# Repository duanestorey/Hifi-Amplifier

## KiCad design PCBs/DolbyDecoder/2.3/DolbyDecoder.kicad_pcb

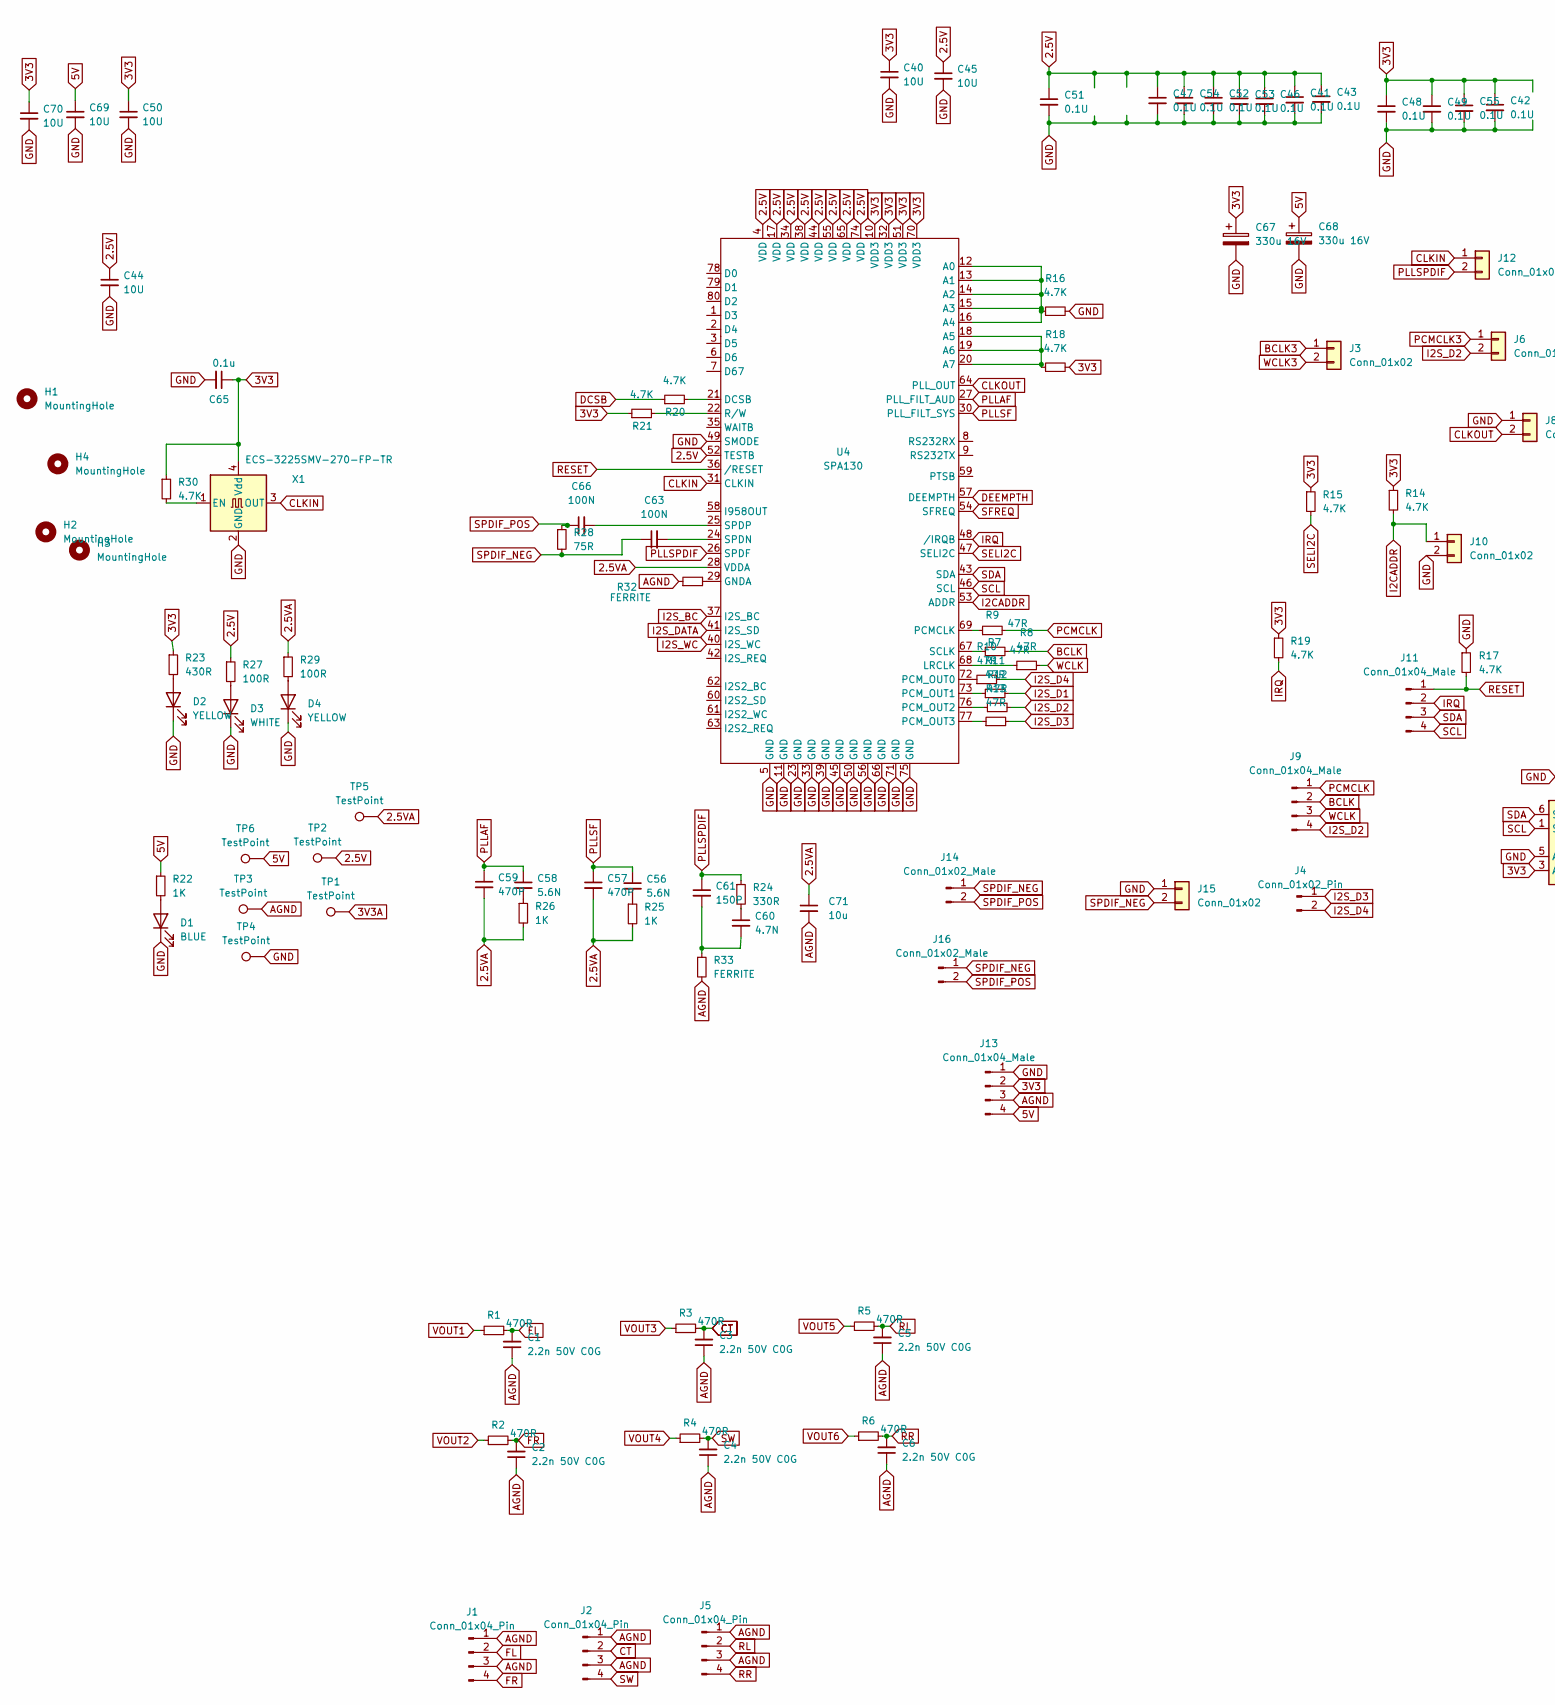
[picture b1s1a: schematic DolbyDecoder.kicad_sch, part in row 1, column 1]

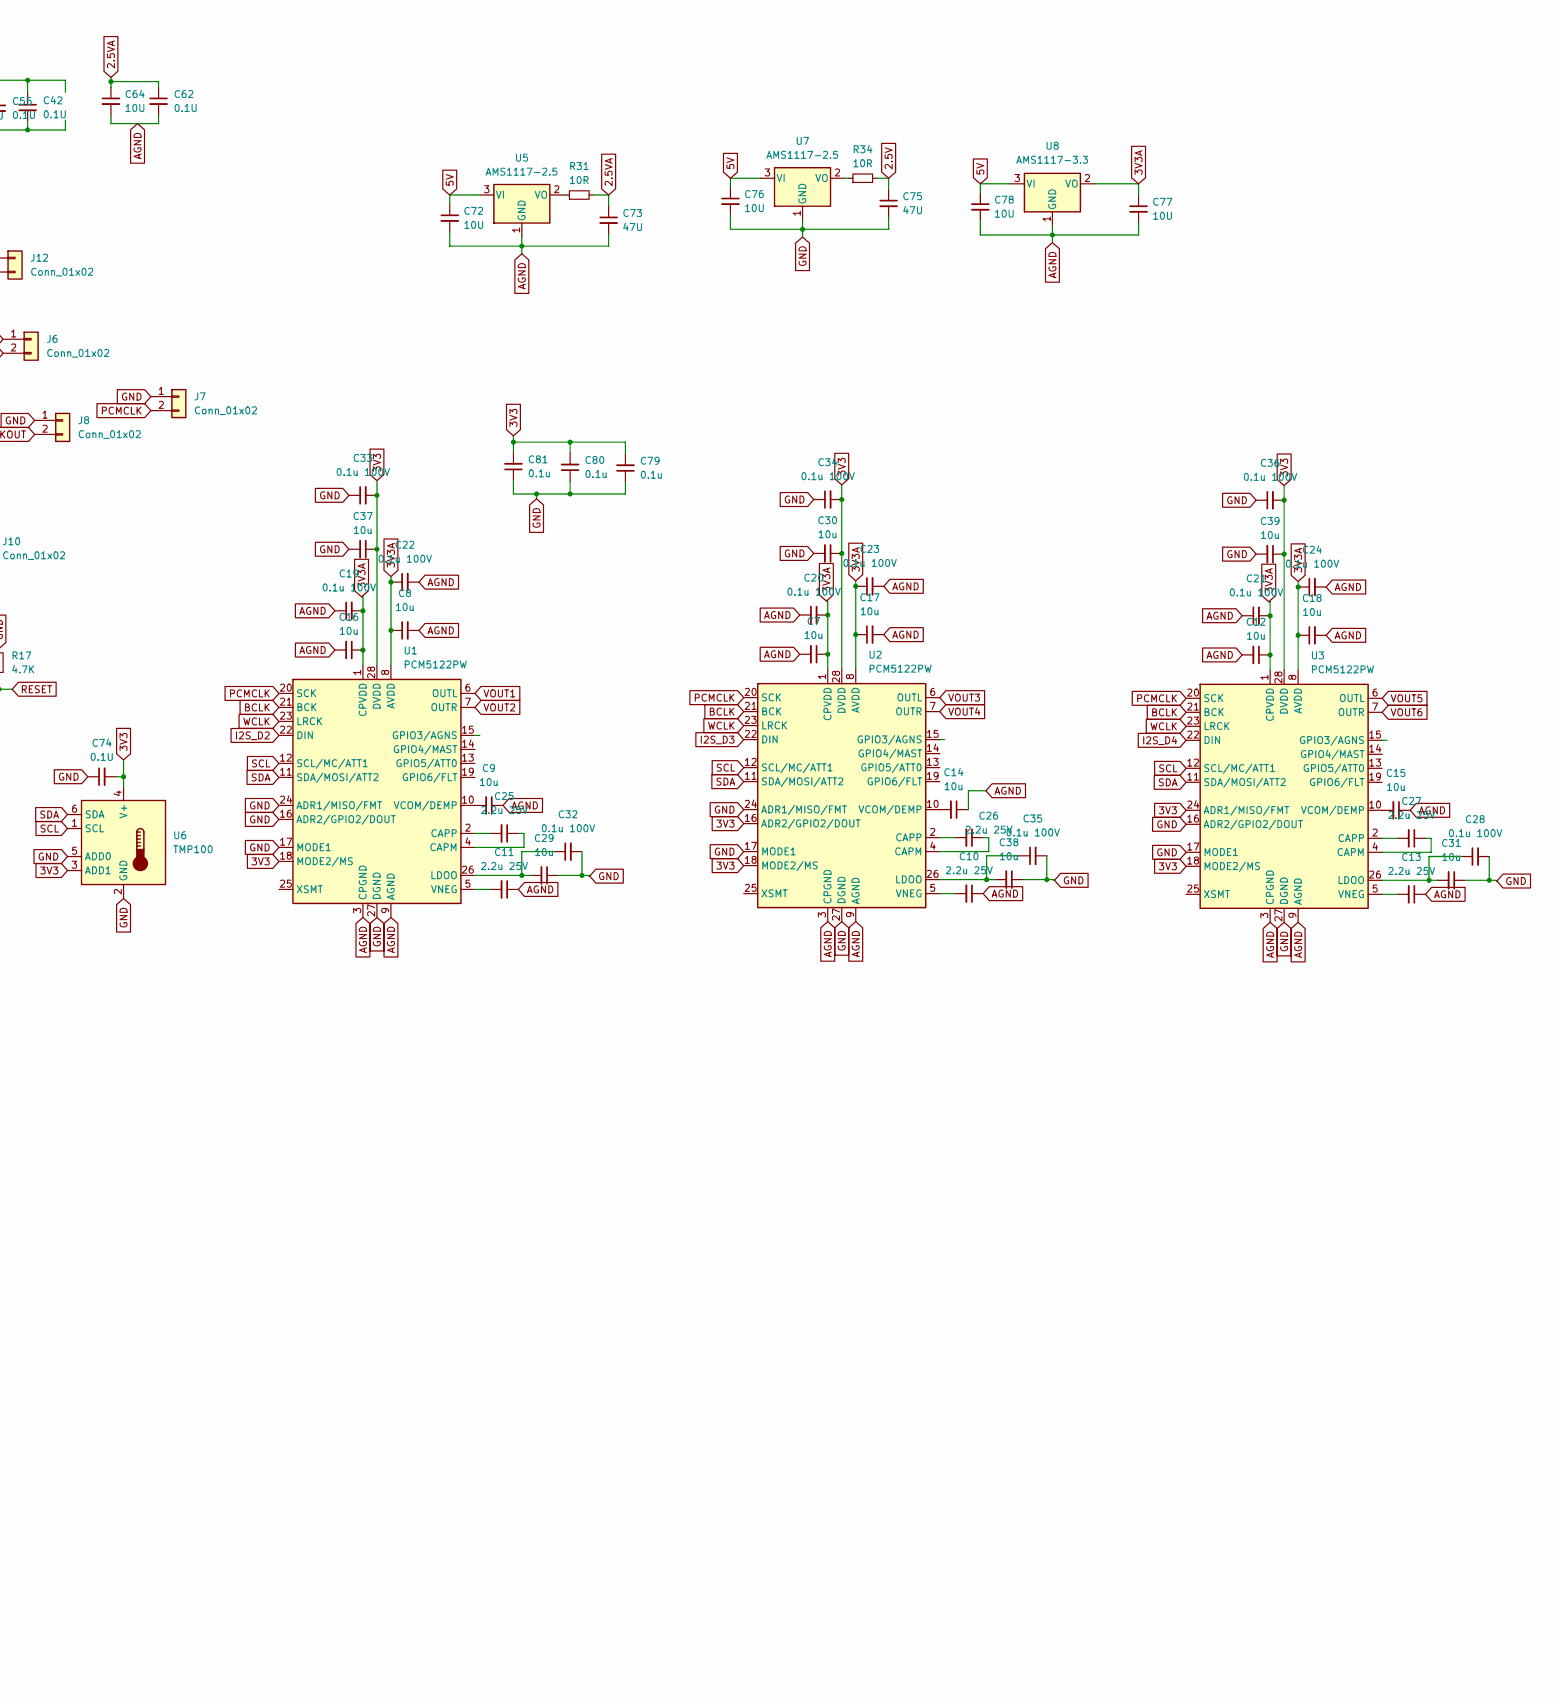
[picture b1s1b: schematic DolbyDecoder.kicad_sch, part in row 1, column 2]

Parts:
C1, C2, C3, C4, C5, C6: 2.2n 50V C0G; C_1206_3216Metric_Pad1.33x1.80mm_HandSolder
C7, C8, C9, C12, C14, C15, C16, C17, C18, C29, C30, C31, C37, C38, C39, C71: 10u; C_1206_3216Metric_Pad1.33x1.80mm_HandSolder
C10, C11, C13, C25, C26, C27: 2.2u 25V; C_1206_3216Metric_Pad1.33x1.80mm_HandSolder
C19, C20, C21, C22, C23, C24, C28, C32, C33, C34, C35, C36: 0.1u 100V; C_0805_2012Metric_Pad1.18x1.45mm_HandSolder
C40, C44, C45, C50, C64, C69, C70, C72, C76, C77, C78: 10U; C_1206_3216Metric_Pad1.33x1.80mm_HandSolder
C41, C42, C43, C46, C47, C48, C49, C51, C52, C53, C54, C55, C62, C74: 0.1U; C_0805_2012Metric_Pad1.18x1.45mm_HandSolder
C56, C58: 5.6N; C_0805_2012Metric_Pad1.18x1.45mm_HandSolder
C57, C59: 470P; C_0805_2012Metric_Pad1.18x1.45mm_HandSolder
C60: 4.7N; C_0805_2012Metric_Pad1.18x1.45mm_HandSolder
C61: 150P; C_0805_2012Metric_Pad1.18x1.45mm_HandSolder
C63, C66: 100N; C_0805_2012Metric_Pad1.18x1.45mm_HandSolder
C65, C79, C80, C81: 0.1u; C_0805_2012Metric_Pad1.18x1.45mm_HandSolder
C67, C68: 330u 16V; CP_Radial_D8.0mm_P2.50mm
C73, C75: 47U; C_1206_3216Metric_Pad1.33x1.80mm_HandSolder
D1: BLUE; LED_0805_2012Metric_Pad1.15x1.40mm_HandSolder
D2, D4: YELLOW; LED_0805_2012Metric_Pad1.15x1.40mm_HandSolder
D3: WHITE; LED_0805_2012Metric_Pad1.15x1.40mm_HandSolder
H1, H2, H3, H4: MountingHole; MountingHole_3.2mm_M3
J1, J2, J5: Conn_01x04_Pin; JST_PH_B4B-PH-K_1x04_P2.00mm_Vertical
J3, J6, J7, J8, J10, J12, J15: Conn_01x02; PinHeader_1x02_P2.54mm_Vertical
J4: Conn_01x02_Pin; PinHeader_1x02_P2.54mm_Vertical
J9: Conn_01x04_Male; PinHeader_1x04_P2.54mm_Vertical
J11: Conn_01x04_Male; JST_PH_B4B-PH-K_1x04_P2.00mm_Vertical
J13: Conn_01x04_Male; JST_XH_B4B-XH-A_1x04_P2.50mm_Vertical
J14: Conn_01x02_Male; JST_XH_B2B-XH-A_1x02_P2.50mm_Vertical
J16: Conn_01x02_Male; PinHeader_1x02_P2.54mm_Vertical
R1, R2, R3, R4, R5, R6: 470R; R_1206_3216Metric_Pad1.30x1.75mm_HandSolder
R7, R8, R9, R10, R11, R12, R13: 47R; R_0805_2012Metric_Pad1.20x1.40mm_HandSolder
R14, R15, R16, R17, R18, R19, R20, R21, R30: 4.7K; R_0603_1608Metric_Pad0.98x0.95mm_HandSolder
R22, R25, R26: 1K; R_0603_1608Metric_Pad0.98x0.95mm_HandSolder
R23: 430R; R_0603_1608Metric_Pad0.98x0.95mm_HandSolder
R24: 330R; R_0603_1608Metric_Pad0.98x0.95mm_HandSolder
R27, R29: 100R; R_0603_1608Metric_Pad0.98x0.95mm_HandSolder
R28: 75R; R_0603_1608Metric_Pad0.98x0.95mm_HandSolder
R31, R34: 10R; R_0603_1608Metric_Pad0.98x0.95mm_HandSolder
R32, R33: FERRITE; R_0603_1608Metric_Pad0.98x0.95mm_HandSolder
TP1, TP2, TP3, TP4, TP5, TP6: TestPoint; TestPoint_THTPad_1.5x1.5mm_Drill0.7mm
U1, U2, U3: PCM5122PW; TSSOP-28_4.4x9.7mm_P0.65mm
U4: SPA130; LQFP-80_14x14mm_P0.65mm
U5, U7: AMS1117-2.5; SOT-223
U6: TMP100; SOT-23-6
U8: AMS1117-3.3; SOT-223
X1: ECS-3225SMV-270-FP-TR; Oscillator_SMD_EuroQuartz_XO32-4Pin_3.2x2.5mm_HandSoldering

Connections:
2.5V: C41.1, C43.1, C44.1, C45.1, C46.1, C47.1, C51.1, C52.1, C53.1, C54.1, C75.1, R27.1, R34.2, TP2.1, U4.4 (VDD), U4.17 (VDD), U4.34 (VDD), U4.38 (VDD), U4.44 (VDD), U4.52 (TESTB), U4.55 (VDD), U4.65 (VDD), U4.74 (VDD)
2.5VA: C57.2, C59.2, C62.1, C64.1, C71.1, C73.1, R25.2, R26.2, R29.1, R31.2, TP5.1, U4.28 (VDDA)
3V3: C30.1, C33.2, C34.2, C36.2, C37.1, C39.1, C40.1, C42.1, C48.1, C49.1, C50.1, C55.1, C65.1, C67.1, C70.1, C74.2, C79.2, C80.2, C81.2, J13.2, R14.1, R15.1, R18.2, R19.1, R21.1, R23.1, R30.1, U1.18 (MODE2/MS), U1.28 (DVDD), U2.16 (ADR2/GPIO2/DOUT), U2.18 (MODE2/MS), U2.28 (DVDD), U3.18 (MODE2/MS), U3.24 (ADR1/MISO/FMT), U3.28 (DVDD), U4.10 (VDD3), U4.32 (VDD3), U4.51 (VDD3), U4.70 (VDD3), U6.3 (ADD1), U6.4 (V+), X1.4 (Vdd)
3V3A: C7.1, C8.1, C12.1, C16.1, C17.1, C18.1, C19.2, C20.2, C21.2, C22.1, C23.1, C24.1, C77.1, TP1.1, U1.1 (CPVDD), U1.8 (AVDD), U2.1 (CPVDD), U2.8 (AVDD), U3.1 (CPVDD), U3.8 (AVDD), U8.2 (VO)
5V: C68.1, C69.1, C72.1, C76.1, C78.1, J13.4, R22.1, TP6.1, U5.3 (VI), U7.3 (VI), U8.3 (VI)
AGND: C1.1, C2.1, C3.1, C4.1, C5.1, C6.1, C7.2, C8.2, C9.1, C10.1, C11.1, C12.2, C13.1, C14.1, C15.1, C16.2, C17.2, C18.2, C19.1, C20.1, C21.1, C22.2, C23.2, C24.2, C62.2, C64.2, C71.2, C72.2, C73.2, C77.2, C78.2, J1.1, J1.3, J2.1, J2.3, J5.1, J5.3, J13.3, R32.1, R33.2, TP3.1, U1.3 (CPGND), U1.9 (AGND), U2.3 (CPGND), U2.9 (AGND), U3.3 (CPGND), U3.9 (AGND), U5.1 (GND), U8.1 (GND)
BCLK: J9.2, R7.2, U1.21 (BCK), U2.21 (BCK), U3.21 (BCK)
BCLK3: J3.1
CLKIN: J12.1, U4.31 (CLKIN), X1.3 (OUT)
CLKOUT: J8.2, U4.64 (PLL_OUT)
CT: C3.2, J2.2, R3.2
DCSB: R20.1
DEEMPTH: U4.57 (DEEMPTH)
FL: C1.2, J1.2, R1.2
FR: C2.2, J1.4, R2.2
GND: C28.2, C29.1, C30.2, C31.1, C32.2, C33.1, C34.1, C35.2, C36.1, C37.2, C38.1, C39.2, C40.2, C41.2, C42.2, C43.2, C44.2, C45.2, C46.2, C47.2, C48.2, C49.2, C50.2, C51.2, C52.2, C53.2, C54.2, C55.2, C65.2, C67.2, C68.2, C69.2, C70.2, C74.1, C75.2, C76.2, C79.1, C80.1, C81.1, D1.1 (K), D2.1 (K), D3.1 (K), D4.1 (K), J7.1, J8.1, J10.2, J13.1, J15.1, R16.2, R17.1, TP4.1, U1.16 (ADR2/GPIO2/DOUT), U1.17 (MODE1), U1.24 (ADR1/MISO/FMT), U1.27 (DGND), U2.17 (MODE1), U2.24 (ADR1/MISO/FMT), U2.27 (DGND), U3.16 (ADR2/GPIO2/DOUT), U3.17 (MODE1), U3.27 (DGND), U4.5 (GND), U4.11 (GND), U4.23 (GND), U4.33 (GND), U4.39 (GND), U4.45 (GND), U4.49 (SMODE), U4.50 (GND), U4.56 (GND), U4.66 (GND), U4.71 (GND), U4.75 (GND), U6.2 (GND), U6.5 (ADD0), U7.1 (GND), X1.2 (GND)
I2CADDR: J10.1, R14.2, U4.53 (ADDR)
I2S_BC: U4.37 (I2S_BC)
I2S_D1: R11.2
I2S_D2: J6.2, J9.4, R12.2, U1.22 (DIN)
I2S_D3: J4.1, R13.2, U2.22 (DIN)
I2S_D4: J4.2, R10.2, U3.22 (DIN)
I2S_DATA: U4.41 (I2S_SD)
I2S_WC: U4.40 (I2S_WC)
IRQ: J11.2, R19.2, U4.48 (/IRQB)
unnamed: C56.2, R25.1
unnamed: C58.2, R26.1
unnamed: C60.1, R24.2
unnamed: C60.2, C61.2, R33.1
unnamed: D1.2 (A), R22.2
unnamed: D2.2 (A), R23.2
unnamed: D3.2 (A), R27.2
unnamed: D4.2 (A), R29.2
unnamed: C25.1, U1.4 (CAPM)
unnamed: C25.2, U1.2 (CAPP)
unnamed: C29.2, C32.1, U1.26 (LDOO)
unnamed: C9.2, U1.10 (VCOM/DEMP)
unnamed: C11.2, U1.5 (VNEG)
unnamed: C26.1, U2.4 (CAPM)
unnamed: C26.2, U2.2 (CAPP)
unnamed: C35.1, C38.2, U2.26 (LDOO)
unnamed: C14.2, U2.10 (VCOM/DEMP)
unnamed: C10.2, U2.5 (VNEG)
unnamed: C27.1, U3.4 (CAPM)
unnamed: C27.2, U3.2 (CAPP)
unnamed: C28.1, C31.2, U3.26 (LDOO)
unnamed: C15.2, U3.10 (VCOM/DEMP)
unnamed: C13.2, U3.5 (VNEG)
unnamed: R16.1, U4.12 (A0), U4.13 (A1), U4.14 (A2), U4.15 (A3), U4.16 (A4)
unnamed: R18.1, U4.18 (A5), U4.19 (A6), U4.20 (A7)
unnamed: R20.2, U4.21 (DCSB)
unnamed: R32.2, U4.29 (GNDA)
unnamed: R8.1, U4.68 (LRCLK)
unnamed: R9.1, U4.69 (PCMCLK)
unnamed: R10.1, U4.72 (PCM_OUT0)
unnamed: R11.1, U4.73 (PCM_OUT1)
unnamed: R12.1, U4.76 (PCM_OUT2)
unnamed: R13.1, U4.77 (PCM_OUT3)
unnamed: R21.2, U4.22 (R/W)
unnamed: R7.1, U4.67 (SCLK)
unnamed: C63.2, U4.24 (SPDN)
unnamed: C66.2, U4.25 (SPDP)
unnamed: R31.1, U5.2 (VO)
unnamed: R34.1, U7.2 (VO)
unnamed: R30.2, X1.1 (EN)
PCMCLK: J7.2, J9.1, R9.2, U1.20 (SCK), U2.20 (SCK), U3.20 (SCK)
PCMCLK3: J6.1
PLLAF: C58.1, C59.1, U4.27 (PLL_FILT_AUD)
PLLSF: C56.1, C57.1, U4.30 (PLL_FILT_SYS)
PLLSPDIF: C61.1, J12.2, R24.1, U4.26 (SPDF)
RESET: J11.1, R17.2, U4.36 (/RESET)
RL: C5.2, J5.2, R5.2
RR: C6.2, J5.4, R6.2
SCL: J11.4, U1.12 (SCL/MC/ATT1), U2.12 (SCL/MC/ATT1), U3.12 (SCL/MC/ATT1), U4.46 (SCL), U6.1 (SCL)
SDA: J11.3, U1.11 (SDA/MOSI/ATT2), U2.11 (SDA/MOSI/ATT2), U3.11 (SDA/MOSI/ATT2), U4.43 (SDA), U6.6 (SDA)
SELI2C: R15.2, U4.47 (SELI2C)
SFREQ: U4.54 (SFREQ)
SPDIF_NEG: C63.1, J14.1, J15.2, J16.1, R28.2
SPDIF_POS: C66.1, J14.2, J16.2, R28.1
SW: C4.2, J2.4, R4.2
VOUT1: R1.1, U1.6 (OUTL)
VOUT2: R2.1, U1.7 (OUTR)
VOUT3: R3.1, U2.6 (OUTL)
VOUT4: R4.1, U2.7 (OUTR)
VOUT5: R5.1, U3.6 (OUTL)
VOUT6: R6.1, U3.7 (OUTR)
WCLK: J9.3, R8.2, U1.23 (LRCK), U2.23 (LRCK), U3.23 (LRCK)
WCLK3: J3.2

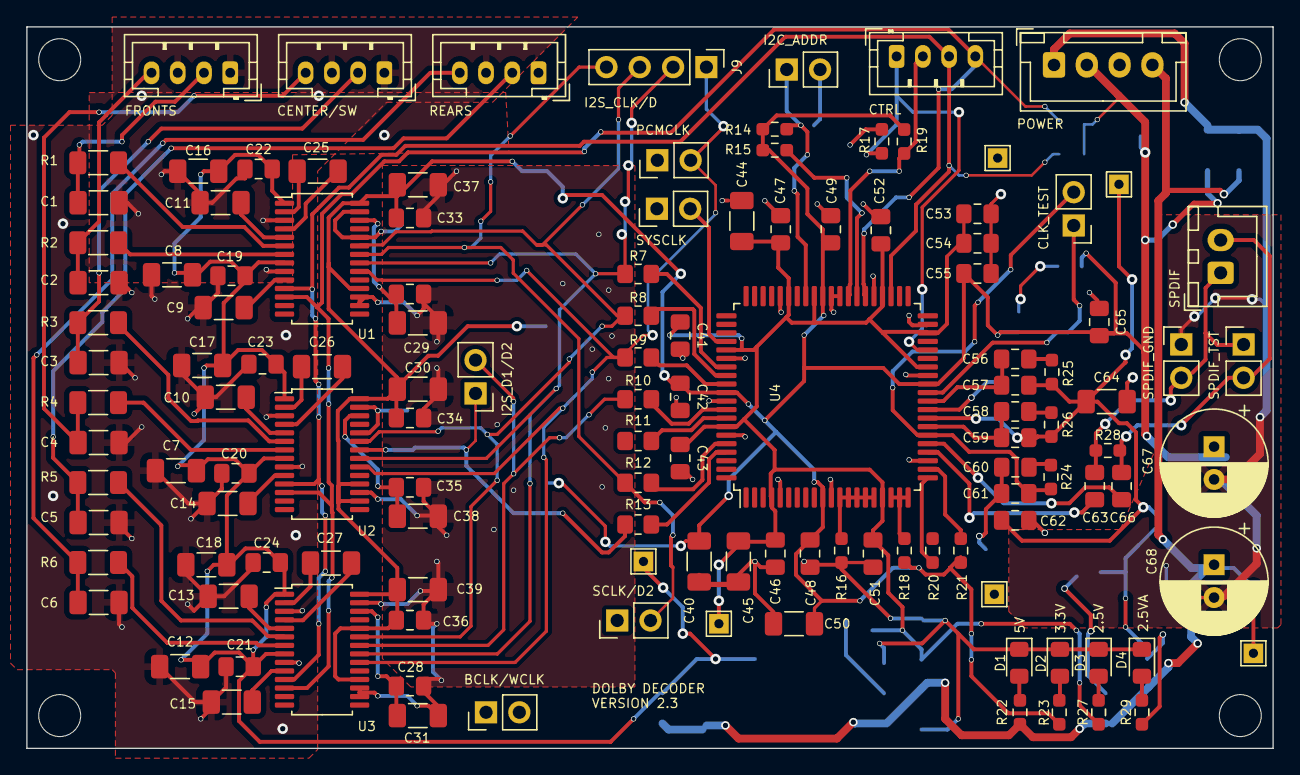
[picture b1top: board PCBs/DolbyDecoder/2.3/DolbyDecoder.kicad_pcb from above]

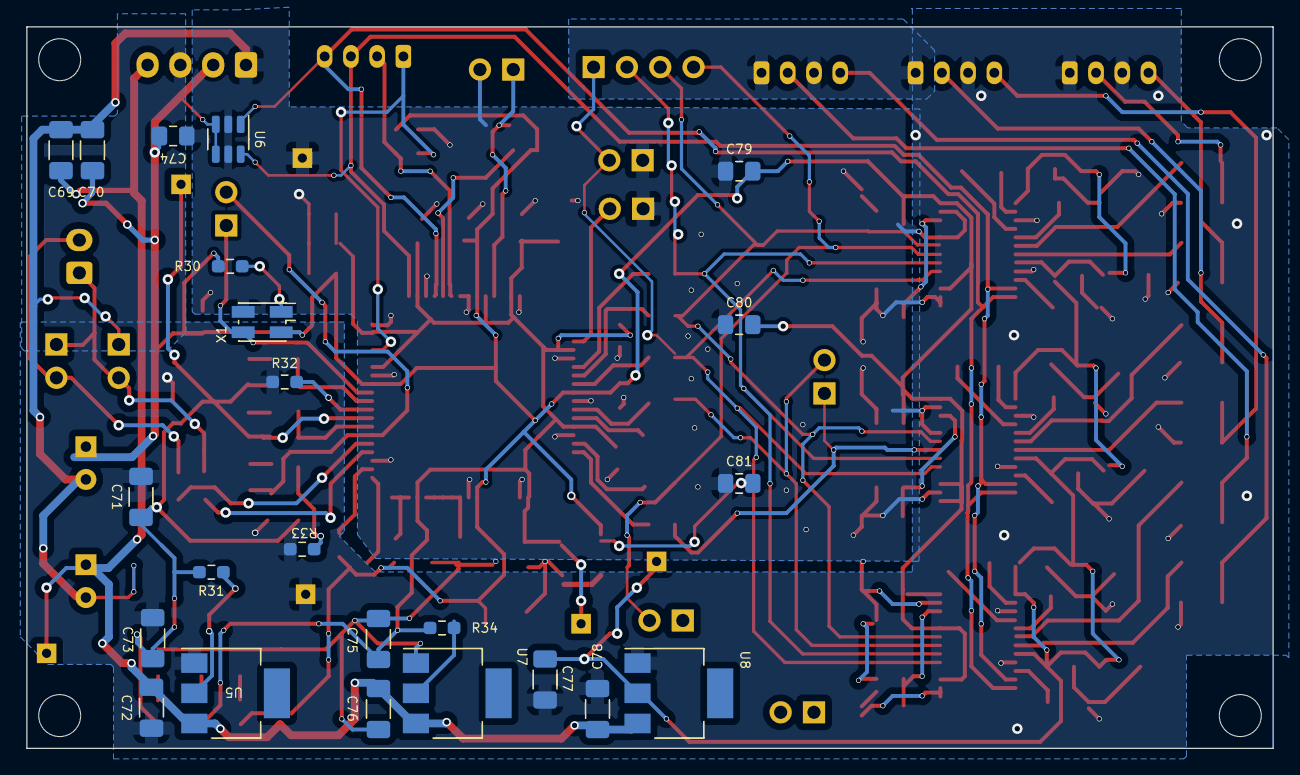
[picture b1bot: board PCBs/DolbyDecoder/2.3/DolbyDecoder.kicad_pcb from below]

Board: 2 copper layers, 95.0 x 55.0 mm, 154 parts (23 on the bottom side), 78 nets.

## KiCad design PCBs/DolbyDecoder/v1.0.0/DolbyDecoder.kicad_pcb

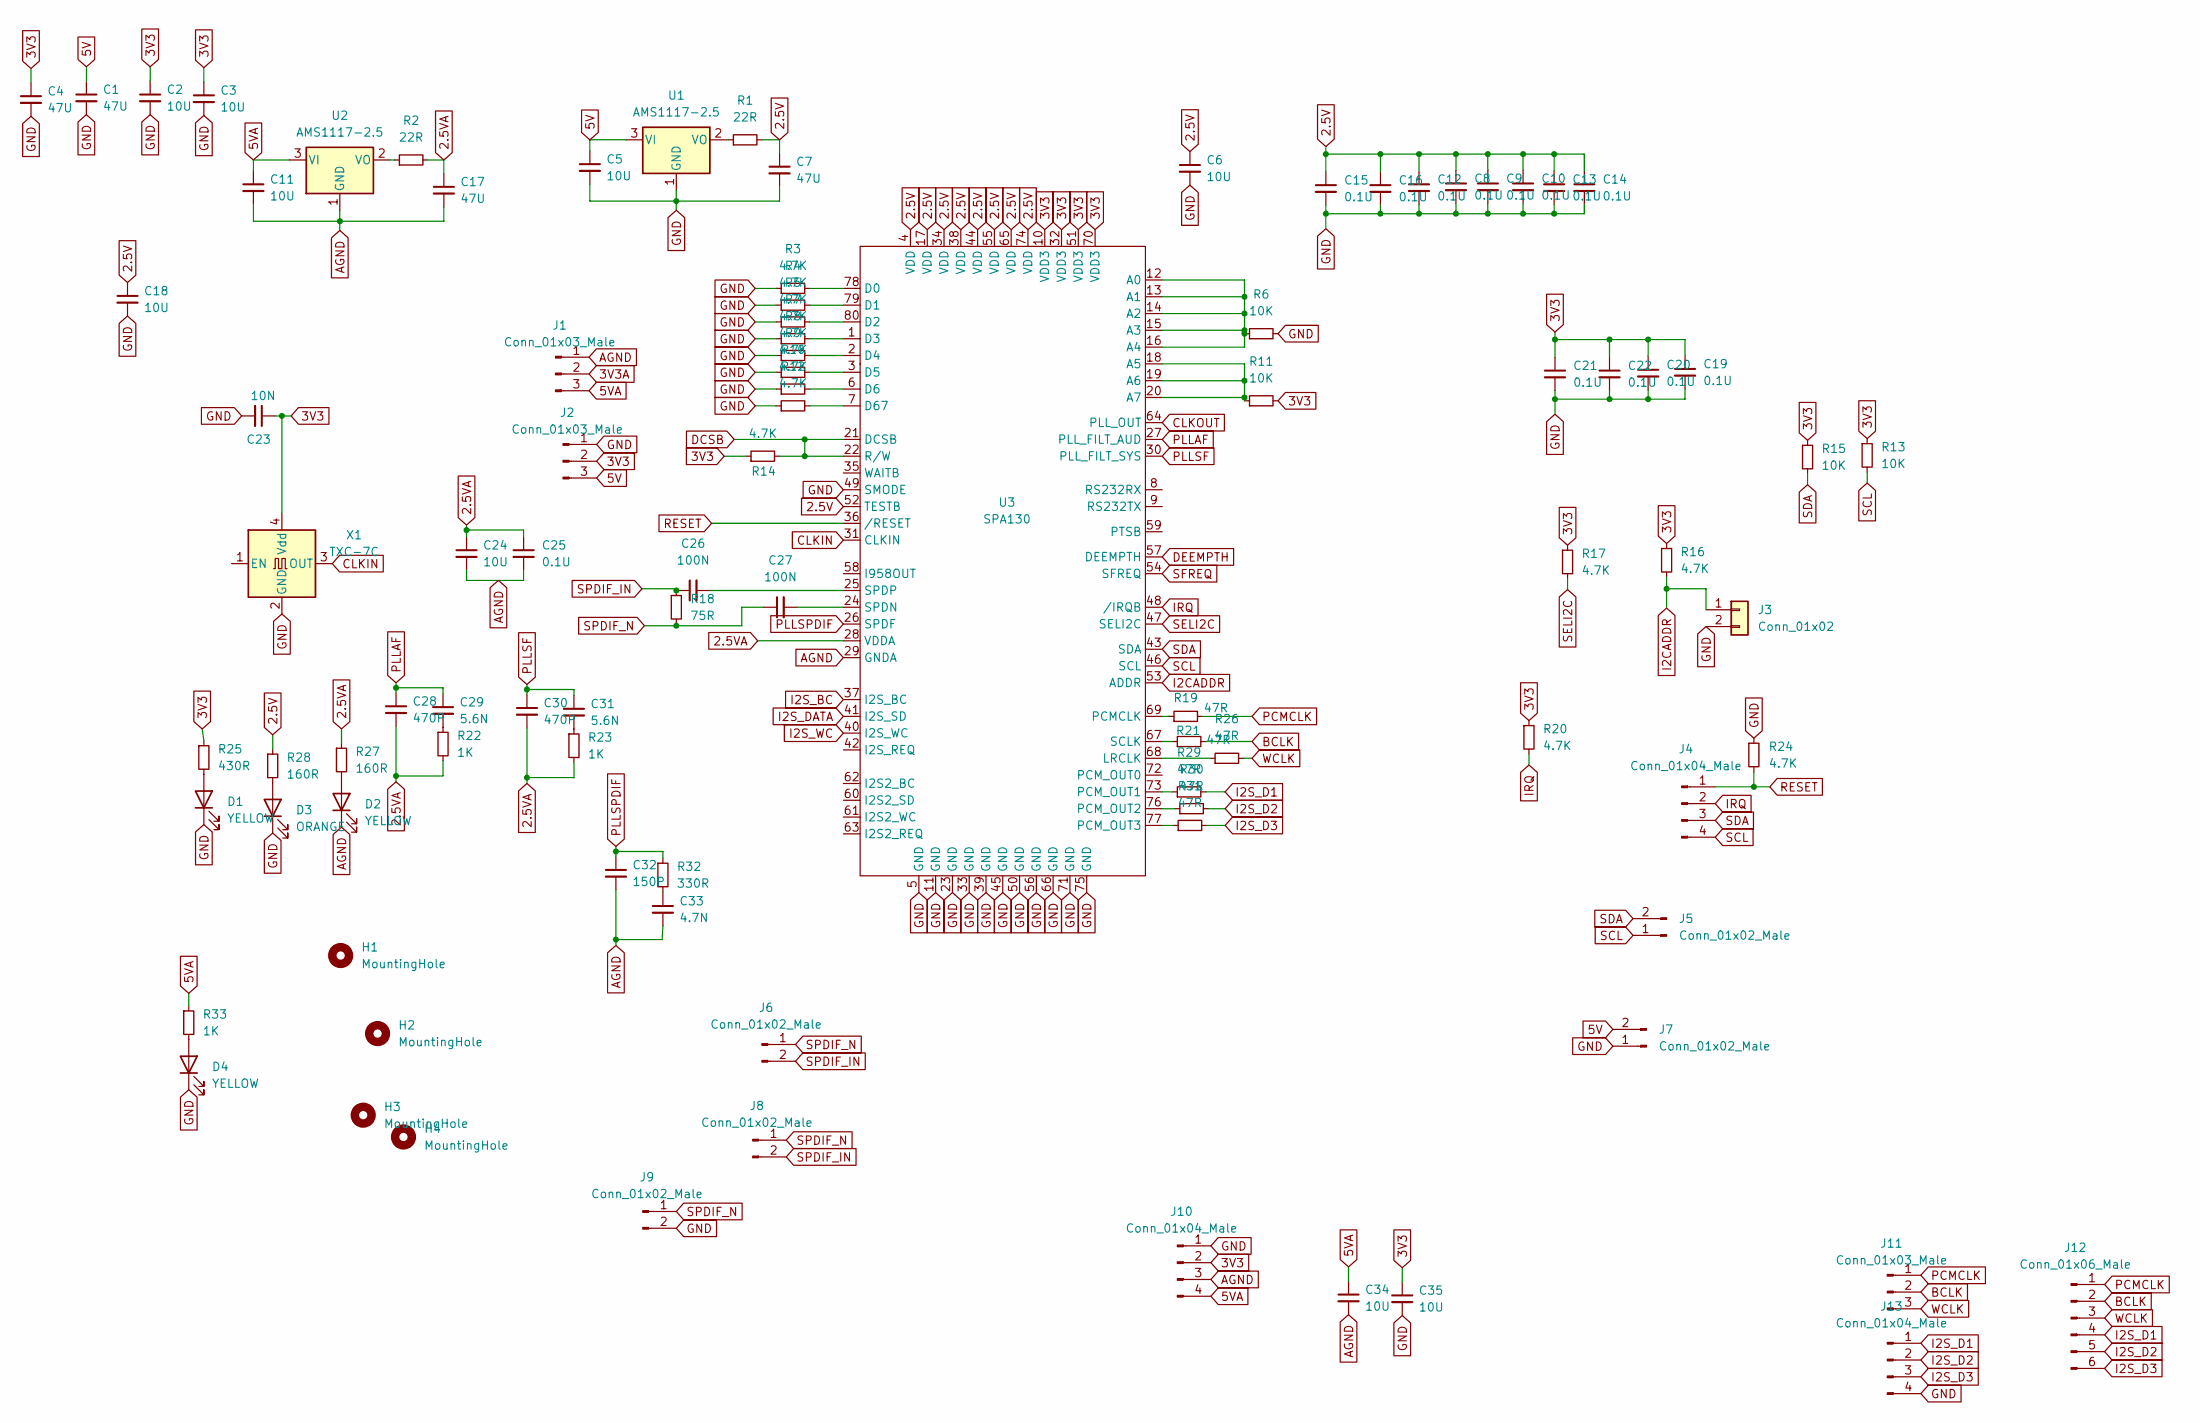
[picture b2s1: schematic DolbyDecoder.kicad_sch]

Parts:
C1, C4, C7, C17: 47U; C_1206_3216Metric_Pad1.33x1.80mm_HandSolder
C2, C3, C6, C18, C34, C35: 10U; C_1206_3216Metric_Pad1.33x1.80mm_HandSolder
C5, C11, C24: 10U; C_0805_2012Metric_Pad1.18x1.45mm_HandSolder
C8, C9, C10, C12, C13, C14, C15, C16, C19, C20, C21, C22, C25: 0.1U; C_0603_1608Metric_Pad1.08x0.95mm_HandSolder
C23: 10N; C_0603_1608Metric_Pad1.08x0.95mm_HandSolder
C26, C27: 100N; C_0805_2012Metric_Pad1.18x1.45mm_HandSolder
C28, C30: 470P; C_0805_2012Metric_Pad1.18x1.45mm_HandSolder
C29, C31: 5.6N; C_0805_2012Metric_Pad1.18x1.45mm_HandSolder
C32: 150P; C_0805_2012Metric_Pad1.18x1.45mm_HandSolder
C33: 4.7N; C_0805_2012Metric_Pad1.18x1.45mm_HandSolder
D1, D2, D4: YELLOW; LED_0805_2012Metric_Pad1.15x1.40mm_HandSolder
D3: ORANGE; LED_0805_2012Metric_Pad1.15x1.40mm_HandSolder
H1, H2, H3, H4: MountingHole; MountingHole_3.2mm_M3
J1, J2, J11: Conn_01x03_Male; JST_PH_B3B-PH-K_1x03_P2.00mm_Vertical
J3: Conn_01x02; PinHeader_1x02_P2.54mm_Vertical
J4, J10, J13: Conn_01x04_Male; JST_PH_B4B-PH-K_1x04_P2.00mm_Vertical
J5, J6, J7: Conn_01x02_Male; JST_PH_B2B-PH-K_1x02_P2.00mm_Vertical
J8, J9: Conn_01x02_Male; PinHeader_1x02_P2.54mm_Vertical
J12: Conn_01x06_Male; PinHeader_1x06_P2.54mm_Vertical
R1, R2: 22R; R_0805_2012Metric_Pad1.20x1.40mm_HandSolder
R3, R4, R5, R7, R8, R9, R10, R12, R14, R16, R17, R20, R24: 4.7K; R_0603_1608Metric_Pad0.98x0.95mm_HandSolder
R6, R11, R13, R15: 10K; R_0603_1608Metric_Pad0.98x0.95mm_HandSolder
R18: 75R; R_0603_1608Metric_Pad0.98x0.95mm_HandSolder
R19, R21, R26, R29, R30, R31: 47R; R_0805_2012Metric_Pad1.20x1.40mm_HandSolder
R22, R23, R33: 1K; R_0603_1608Metric_Pad0.98x0.95mm_HandSolder
R25: 430R; R_0603_1608Metric_Pad0.98x0.95mm_HandSolder
R27, R28: 160R; R_0603_1608Metric_Pad0.98x0.95mm_HandSolder
R32: 330R; R_0603_1608Metric_Pad0.98x0.95mm_HandSolder
U1, U2: AMS1117-2.5; SOT-223
U3: SPA130; LQFP-80_14x14mm_P0.65mm
X1: TXC-7C; Oscillator_SMD_EuroQuartz_XO32-4Pin_3.2x2.5mm_HandSoldering

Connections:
2.5V: C6.1, C7.1, C8.1, C9.1, C10.1, C12.1, C13.1, C14.1, C15.1, C16.1, C18.1, R1.2, R28.1, U3.4 (VDD), U3.17 (VDD), U3.34 (VDD), U3.38 (VDD), U3.44 (VDD), U3.52 (TESTB), U3.55 (VDD), U3.65 (VDD), U3.74 (VDD)
2.5VA: C17.1, C24.1, C25.1, C28.2, C30.2, R2.2, R22.2, R23.2, R27.1, U3.28 (VDDA)
3V3: C2.1, C3.1, C4.1, C19.1, C20.1, C21.1, C22.1, C23.1, C35.1, J2.2, J10.2, R11.2, R13.1, R14.1, R15.1, R16.1, R17.1, R20.1, R25.1, U3.10 (VDD3), U3.32 (VDD3), U3.51 (VDD3), U3.70 (VDD3), X1.4 (Vdd)
3V3A: J1.2
5V: C1.1, C5.1, J2.3, J7.2, U1.3 (VI)
5VA: C11.1, C34.1, J1.3, J10.4, R33.1, U2.3 (VI)
AGND: C11.2, C17.2, C24.2, C25.2, C32.2, C33.2, C34.2, D2.1 (K), J1.1, J10.3, U2.1 (GND), U3.29 (GNDA)
BCLK: J11.2, J12.2, R21.2
CLKIN: U3.31 (CLKIN), X1.3 (OUT)
CLKOUT: U3.64 (PLL_OUT)
DCSB: R14.2, U3.21 (DCSB), U3.22 (R/W)
DEEMPTH: U3.57 (DEEMPTH)
GND: C1.2, C2.2, C3.2, C4.2, C5.2, C6.2, C7.2, C8.2, C9.2, C10.2, C12.2, C13.2, C14.2, C15.2, C16.2, C18.2, C19.2, C20.2, C21.2, C22.2, C23.2, C35.2, D1.1 (K), D3.1 (K), D4.1 (K), J2.1, J3.2, J7.1, J9.2, J10.1, J13.4, R3.1, R4.1, R5.1, R6.2, R7.1, R8.1, R9.1, R10.1, R12.1, R24.1, U1.1 (GND), U3.5 (GND), U3.11 (GND), U3.23 (GND), U3.33 (GND), U3.39 (GND), U3.45 (GND), U3.49 (SMODE), U3.50 (GND), U3.56 (GND), U3.66 (GND), U3.71 (GND), U3.75 (GND), X1.2 (GND)
I2CADDR: J3.1, R16.2, U3.53 (ADDR)
I2S_BC: U3.37 (I2S_BC)
I2S_D1: J12.4, J13.1, R29.2
I2S_D2: J12.5, J13.2, R30.2
I2S_D3: J12.6, J13.3, R31.2
I2S_DATA: U3.41 (I2S_SD)
I2S_WC: U3.40 (I2S_WC)
IRQ: J4.2, R20.2, U3.48 (/IRQB)
unnamed: C26.2, U3.25 (SPDP)
unnamed: C27.2, U3.24 (SPDN)
unnamed: C29.2, R22.1
unnamed: C31.2, R23.1
unnamed: C33.1, R32.2
unnamed: D1.2 (A), R25.2
unnamed: D2.2 (A), R27.2
unnamed: D3.2 (A), R28.2
unnamed: D4.2 (A), R33.2
unnamed: R1.1, U1.2 (VO)
unnamed: R2.1, U2.2 (VO)
unnamed: R3.2, U3.78 (D0)
unnamed: R4.2, U3.79 (D1)
unnamed: R5.2, U3.80 (D2)
unnamed: R6.1, U3.12 (A0), U3.13 (A1), U3.14 (A2), U3.15 (A3), U3.16 (A4)
unnamed: R7.2, U3.1 (D3)
unnamed: R8.2, U3.2 (D4)
unnamed: R9.2, U3.3 (D5)
unnamed: R10.2, U3.6 (D6)
unnamed: R11.1, U3.18 (A5), U3.19 (A6), U3.20 (A7)
unnamed: R12.2, U3.7 (D67)
unnamed: R19.1, U3.69 (PCMCLK)
unnamed: R21.1, U3.67 (SCLK)
unnamed: R26.1, U3.68 (LRCLK)
unnamed: R29.1, U3.73 (PCM_OUT1)
unnamed: R30.1, U3.76 (PCM_OUT2)
unnamed: R31.1, U3.77 (PCM_OUT3)
PCMCLK: J11.1, J12.1, R19.2
PLLAF: C28.1, C29.1, U3.27 (PLL_FILT_AUD)
PLLSF: C30.1, C31.1, U3.30 (PLL_FILT_SYS)
PLLSPDIF: C32.1, R32.1, U3.26 (SPDF)
RESET: J4.1, R24.2, U3.36 (/RESET)
SCL: J4.4, J5.1, R13.2, U3.46 (SCL)
SDA: J4.3, J5.2, R15.2, U3.43 (SDA)
SELI2C: R17.2, U3.47 (SELI2C)
SFREQ: U3.54 (SFREQ)
SPDIF_IN: C26.1, J6.2, J8.2, R18.1
SPDIF_N: C27.1, J6.1, J8.1, J9.1, R18.2
WCLK: J11.3, J12.3, R26.2

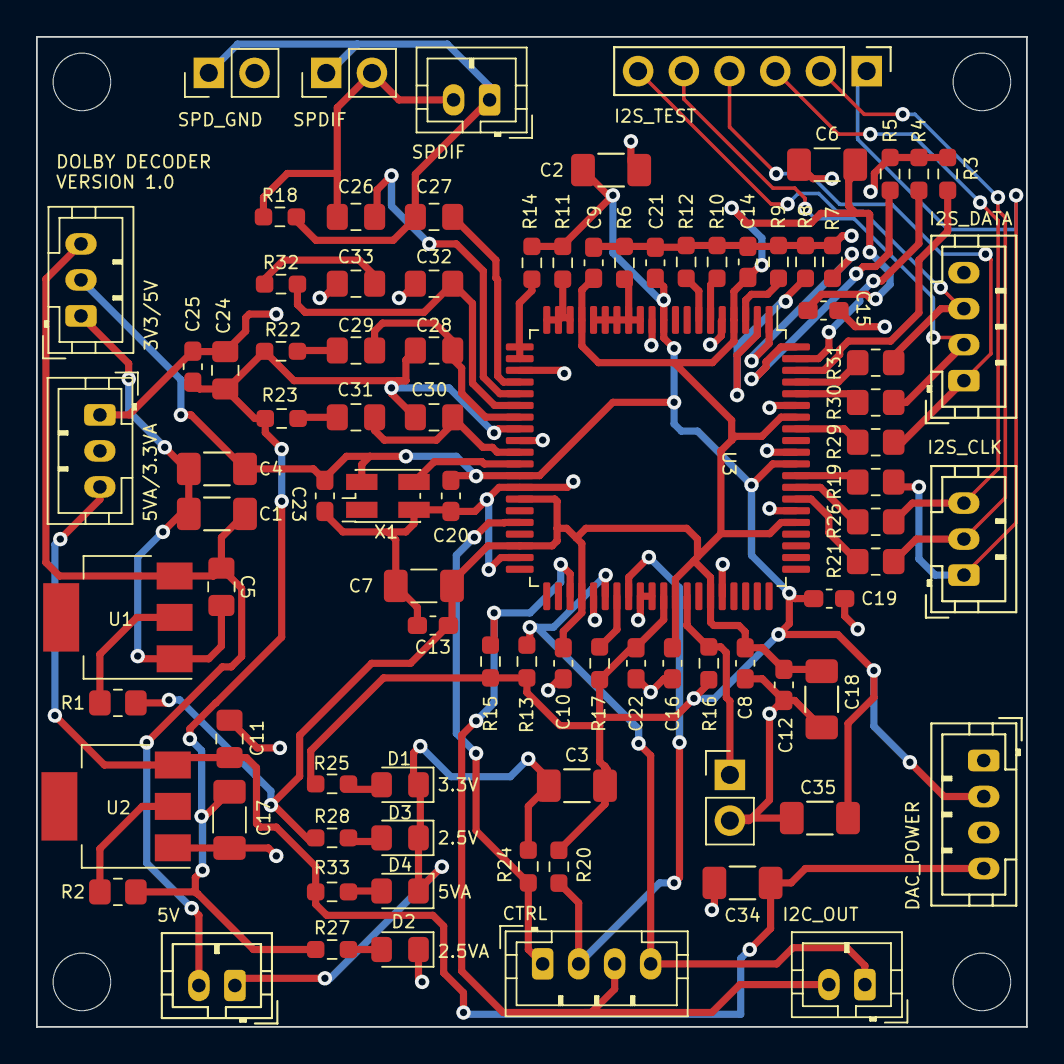
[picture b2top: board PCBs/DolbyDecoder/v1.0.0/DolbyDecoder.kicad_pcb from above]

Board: 2 copper layers, 55.0 x 55.0 mm, 93 parts (0 on the bottom side), 53 nets.
